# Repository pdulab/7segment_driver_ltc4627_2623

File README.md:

# 7segment_driver
A small board to drive the LTC-4627 & LTC-2623 4x7-segments ICs.

## Warning
This board is a work in progress, therefore it might not work properly. No board has been produced yet. Use at your own risk.

## Description
This board was adapted from [Sparkfun's 7-Segment Serial Display](https://www.sparkfun.com/products/11441) (licensed under CC BY-SA 3.0) to work with both the LTC-4627 and LTC-2623 4x7-segments ICs from LiteOn.

To drive the 7-segments IC, it uses an ATmega328.
Left-over GPIOs are broken out on a connector (to be used as input, for example).

##  License
This work is licensed under a [Creative Commons Attribution-ShareAlike 4.0 International License](https://creativecommons.org/licenses/by-sa/4.0/).

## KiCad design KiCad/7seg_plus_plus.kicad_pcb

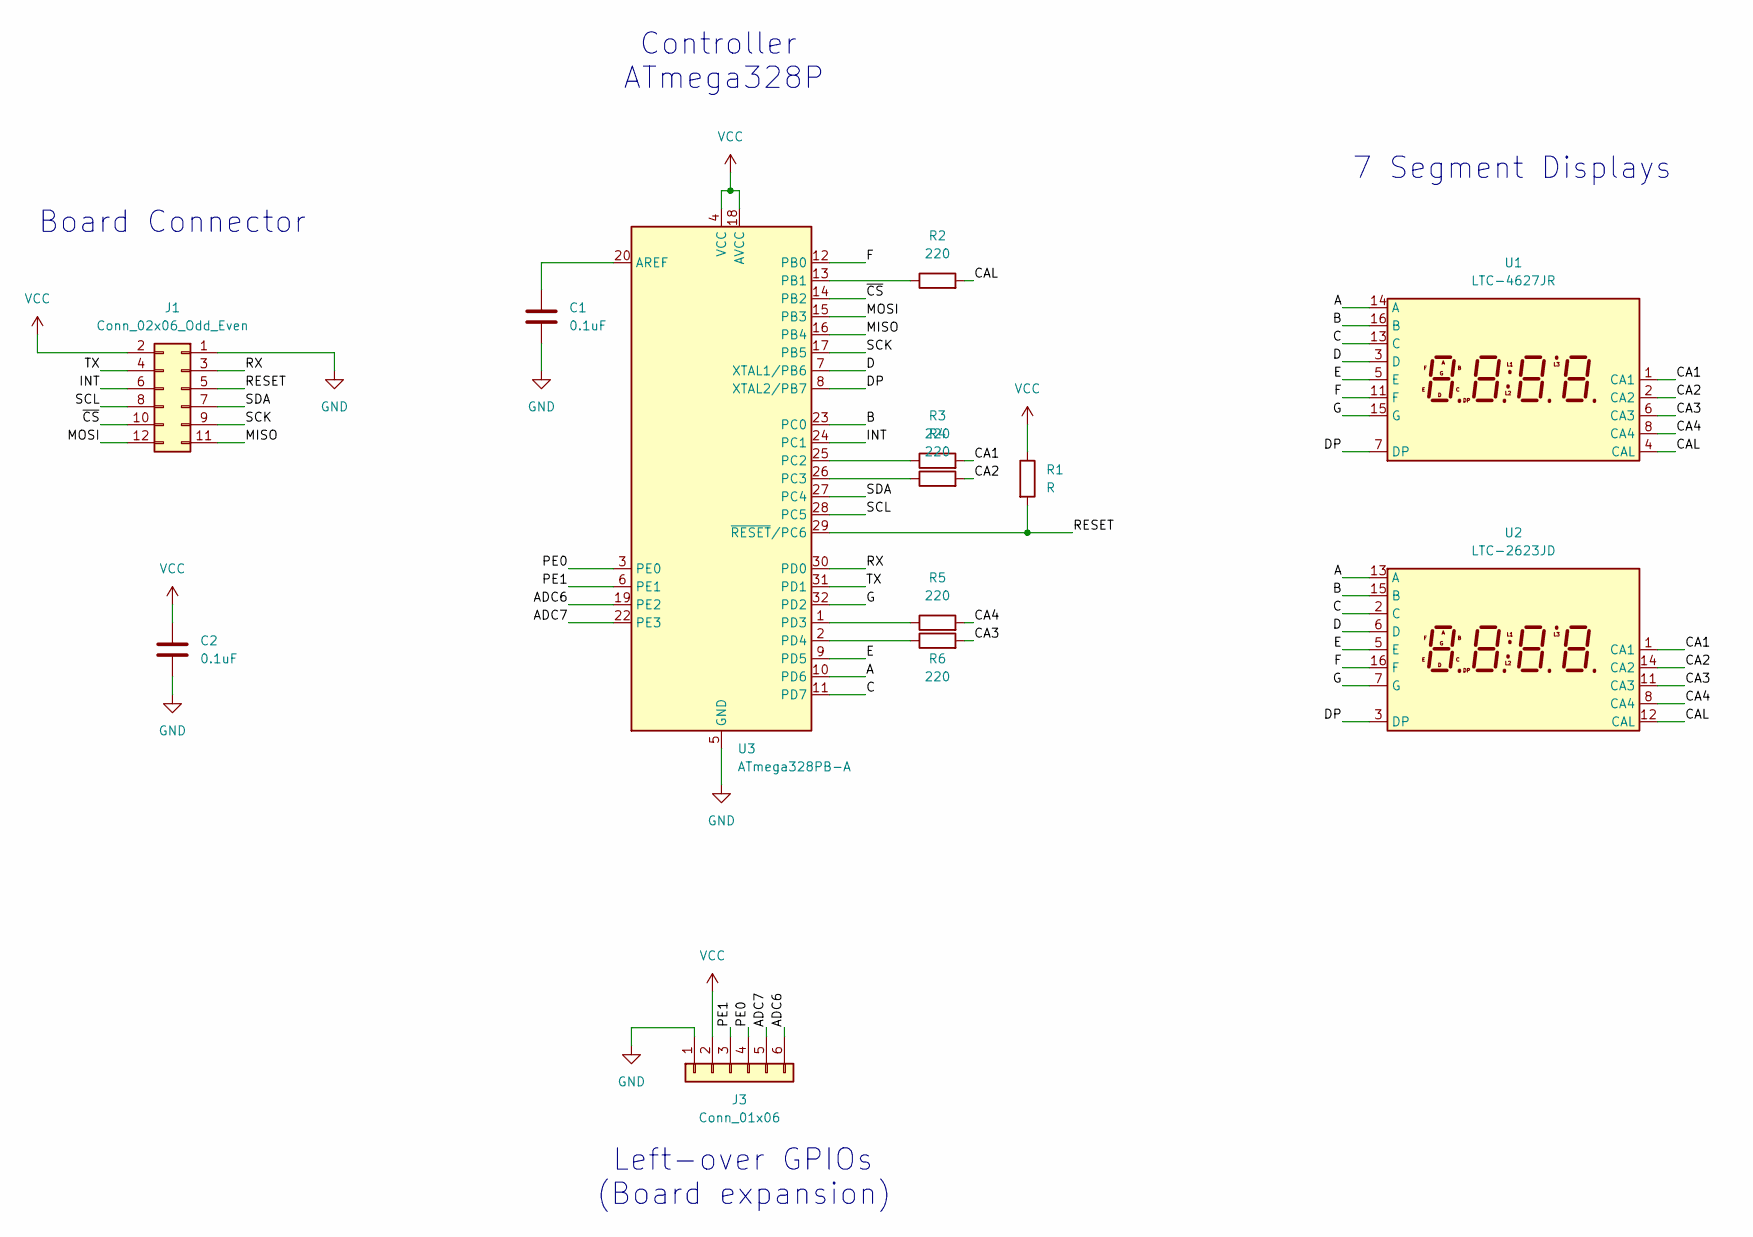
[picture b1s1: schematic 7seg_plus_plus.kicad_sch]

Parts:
C1, C2: 0.1uF; C_1206_3216Metric_Pad1.33x1.80mm_HandSolder
J1: Conn_02x06_Odd_Even; PinHeader_2x06_P2.54mm_Vertical
J3: Conn_01x06; PinHeader_1x06_P2.54mm_Vertical
R1: R; R_1206_3216Metric_Pad1.30x1.75mm_HandSolder
R2, R3, R4, R5, R6: 220; R_1206_3216Metric_Pad1.30x1.75mm_HandSolder
U1: LTC-4627JR; LTC-4627Jx
U2: LTC-2623JD; LTC-2623Jx
U3: ATmega328PB-A; TQFP-32_7x7mm_P0.8mm

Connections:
/A: U1.14 (A), U2.13 (A), U3.10 (PD6)
/ADC6: J3.6, U3.19 (PE2)
/ADC7: J3.5, U3.22 (PE3)
/B: U1.16 (B), U2.15 (B), U3.23 (PC0)
/C: U1.13 (C), U2.2 (C), U3.11 (PD7)
/CA1: R3.2, U1.1 (CA1), U2.1 (CA1)
/CA2: R4.2, U1.2 (CA2), U2.14 (CA2)
/CA3: R6.2, U1.6 (CA3), U2.11 (CA3)
/CA4: R5.2, U1.8 (CA4), U2.8 (CA4)
/CAL: R2.2, U1.4 (CAL), U2.12 (CAL)
/D: U1.3 (D), U2.6 (D), U3.7 (XTAL1/PB6)
/DP: U1.7 (DP), U2.3 (DP), U3.8 (XTAL2/PB7)
/E: U1.5 (E), U2.5 (E), U3.9 (PD5)
/F: U1.11 (F), U2.16 (F), U3.12 (PB0)
/G: U1.15 (G), U2.7 (G), U3.32 (PD2)
/INT: J1.6, U3.24 (PC1)
/MISO: J1.11, U3.16 (PB4)
/MOSI: J1.12, U3.15 (PB3)
/PE0: J3.4, U3.3 (PE0)
/PE1: J3.3, U3.6 (PE1)
/RESET: J1.5, R1.2, U3.29 (~RESET/PC6)
/RX: J1.3, U3.30 (PD0)
/SCK: J1.9, U3.17 (PB5)
/SCL: J1.8, U3.28 (PC5)
/SDA: J1.7, U3.27 (PC4)
/TX: J1.4, U3.31 (PD1)
/~CS: J1.10, U3.14 (PB2)
GND: C1.2, C2.2, J1.1, J3.1, U3.5 (GND), U3.21 (GND)
unnamed: C1.1, U3.20 (AREF)
unnamed: R2.1, U3.13 (PB1)
unnamed: R3.1, U3.25 (PC2)
unnamed: R4.1, U3.26 (PC3)
unnamed: R5.1, U3.1 (PD3)
unnamed: R6.1, U3.2 (PD4)
VCC: C2.1, J1.2, J3.2, R1.1, U3.4 (VCC), U3.18 (AVCC)

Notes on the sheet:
Board Connector
Controller ATmega328P
Left-over GPIOs (Board expansion)
7 Segment Displays

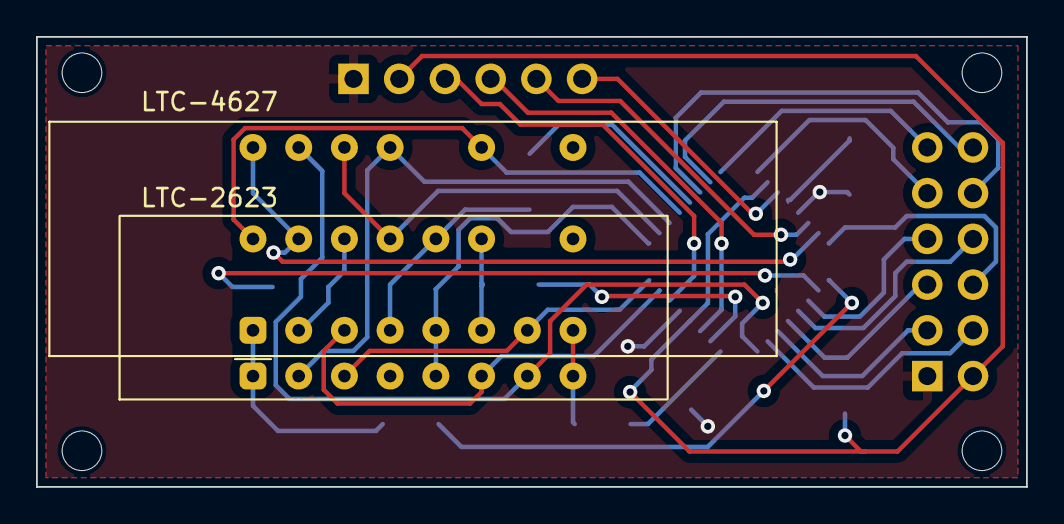
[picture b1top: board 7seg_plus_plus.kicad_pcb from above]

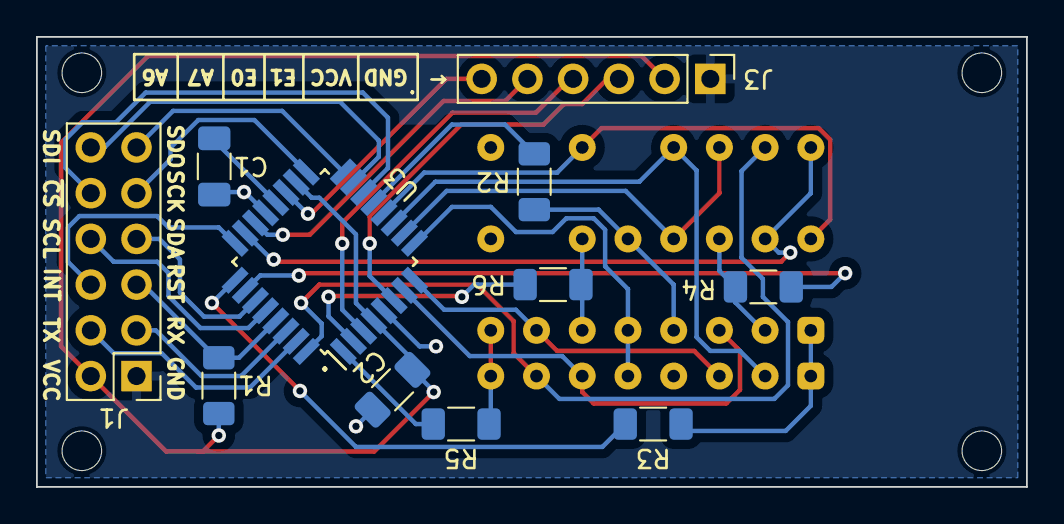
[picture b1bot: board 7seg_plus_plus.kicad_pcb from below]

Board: 2 copper layers, 55.0 x 25.0 mm, 13 parts (11 on the bottom side), 35 nets.

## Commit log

2023-11-26 Create LICENSE
2023-11-26 Minor changes
    - Added FreeCAD temp and backup files to the .gitignore
    - Fixed typo in README.md
2023-11-27 Added Kicad Project and 3D models
